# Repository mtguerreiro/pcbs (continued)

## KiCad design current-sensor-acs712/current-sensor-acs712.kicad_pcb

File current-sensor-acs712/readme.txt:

Current sensor
--------------

The board was designed with ACS712 in mind. However, it will work with the following ACS sensors:
- ACS711
- ACS712
- ACS725
- ACS730
- ACS70331
- ACS71240

The only difference is pin 6, which can be a filter, NC, or a fault signal. Beforing using one of these sensors, consult the datasheet for the proper configuration on the board.

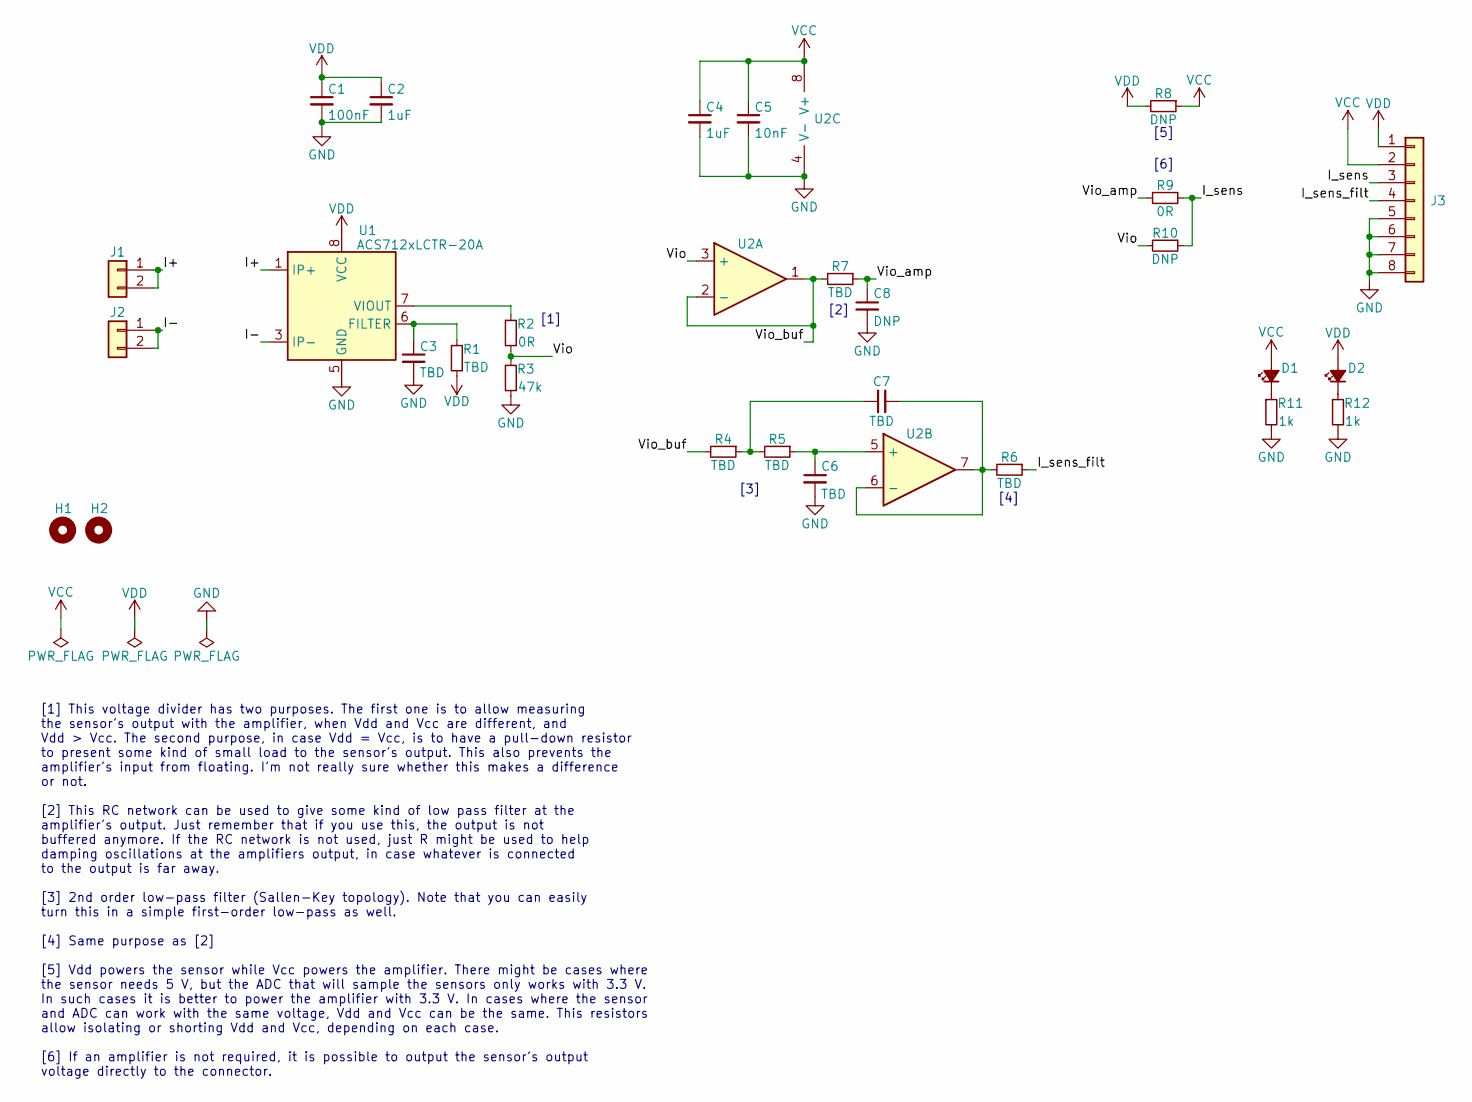
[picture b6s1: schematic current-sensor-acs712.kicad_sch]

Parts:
C1: 100nF; C_0805_2012Metric_Pad1.18x1.45mm_HandSolder
C2, C4: 1uF; C_0805_2012Metric_Pad1.18x1.45mm_HandSolder
C3, C6, C7: TBD; C_0805_2012Metric_Pad1.18x1.45mm_HandSolder
C5: 10nF; C_0805_2012Metric_Pad1.18x1.45mm_HandSolder
C8: DNP; C_0805_2012Metric_Pad1.18x1.45mm_HandSolder
D1, D2: LED_Small_Filled; LED_0805_2012Metric_Pad1.15x1.40mm_HandSolder
H1, H2: MountingHole; MountingHole_3.2mm_M3
J1, J2: Conn_01x02; TerminalBlock_Phoenix_MKDS-1,5-2-5.08_1x02_P5.08mm_Horizont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
J3: Conn_01x08; PinHeader_1x08_P2.54mm_Vertical
R1, R4, R5, R6, R7: TBD; R_0805_2012Metric_Pad1.20x1.40mm_HandSolder
R2, R9: 0R; R_0805_2012Metric_Pad1.20x1.40mm_HandSolder
R3: 47k; R_0805_2012Metric_Pad1.20x1.40mm_HandSolder
R8, R10: DNP; R_0805_2012Metric_Pad1.20x1.40mm_HandSolder
R11, R12: 1k; R_0805_2012Metric_Pad1.20x1.40mm_HandSolder
U1: ACS712xLCTR-20A; SOIC-8_3.9x4.9mm_P1.27mm
U2: Opamp_Dual; SOIC-8_3.9x4.9mm_P1.27mm

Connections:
/I+: J1.1, J1.2, U1.1 (IP+), U1.2 (IP+)
/I-: J2.1, J2.2, U1.3 (IP-), U1.4 (IP-)
/I_sens: J3.3, R9.1, R10.1
/I_sens_filt: J3.4, R6.1
/Vio: R2.2, R3.1, R10.2, U2.3 (+)
/Vio_amp: C8.1, R7.1, R9.2
/Vio_buf: R4.2, R7.2, U2.1, U2.2 (-)
GND: C1.2, C2.2, C3.2, C4.2, C5.2, C6.2, C8.2, J3.5, J3.6, J3.7, J3.8, R3.2, R11.2, R12.2, U1.5 (GND), U2.4 (V-)
unnamed: C3.1, R1.1, U1.6 (FILTER)
unnamed: C6.1, R5.1, U2.5 (+)
unnamed: C7.1, R4.1, R5.2
unnamed: C7.2, R6.2, U2.6 (-), U2.7
unnamed: D1.1 (K), R11.1
unnamed: D2.1 (K), R12.1
unnamed: R2.1, U1.7 (VIOUT)
VCC: C4.1, C5.1, D1.2 (A), J3.2, R8.1, U2.8 (V+)
VDD: C1.1, C2.1, D2.2 (A), J3.1, R1.2, R8.2, U1.8 (VCC)

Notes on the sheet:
[4]
[1]
[3]
[2]
[1] This voltage divider has two purposes. The first one is to allow measuring the sensor's output with the amplifier, when Vdd and Vcc are different, and Vdd > Vcc. The second purpose, in case Vdd = Vcc, is to have a pull-down resistor to present some kind of small load to the sensor's output. Thi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
[6]
[5]

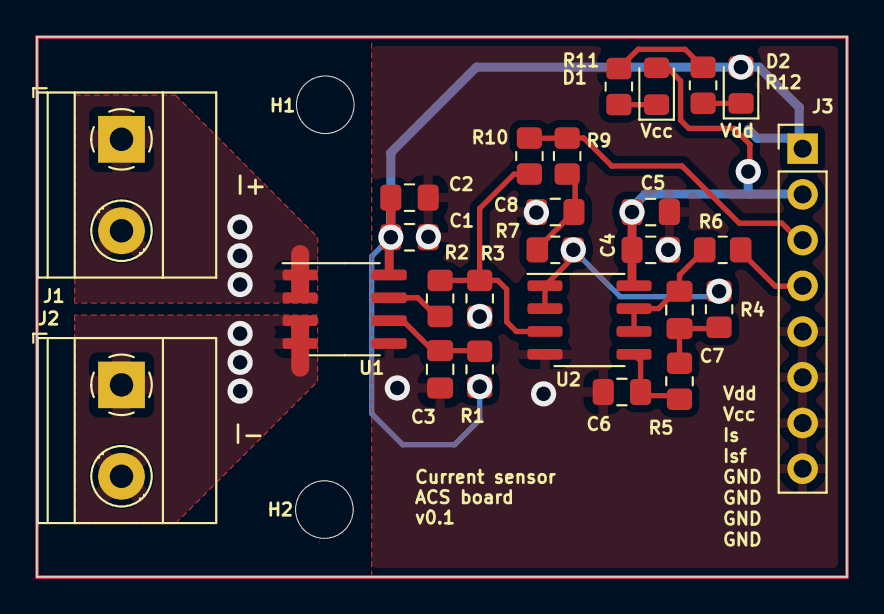
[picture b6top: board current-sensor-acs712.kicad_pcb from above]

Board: 2 copper layers, 45.0 x 30.0 mm, 29 parts (1 on the bottom side), 17 nets.

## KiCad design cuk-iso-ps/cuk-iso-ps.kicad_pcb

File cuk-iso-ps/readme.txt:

Current sensor
--------------

The board was designed with ACS730-20AB in mind. However, it will work with the following ACS sensors:
- ACS711
- ACS712
- ACS725
- ACS730
- ACS70331
- ACS71240

The only difference is pin 6, which can be a filter, NC, or a fault signal. Beforing using one of these sensors, consult the datasheet for the proper configuration on the board.

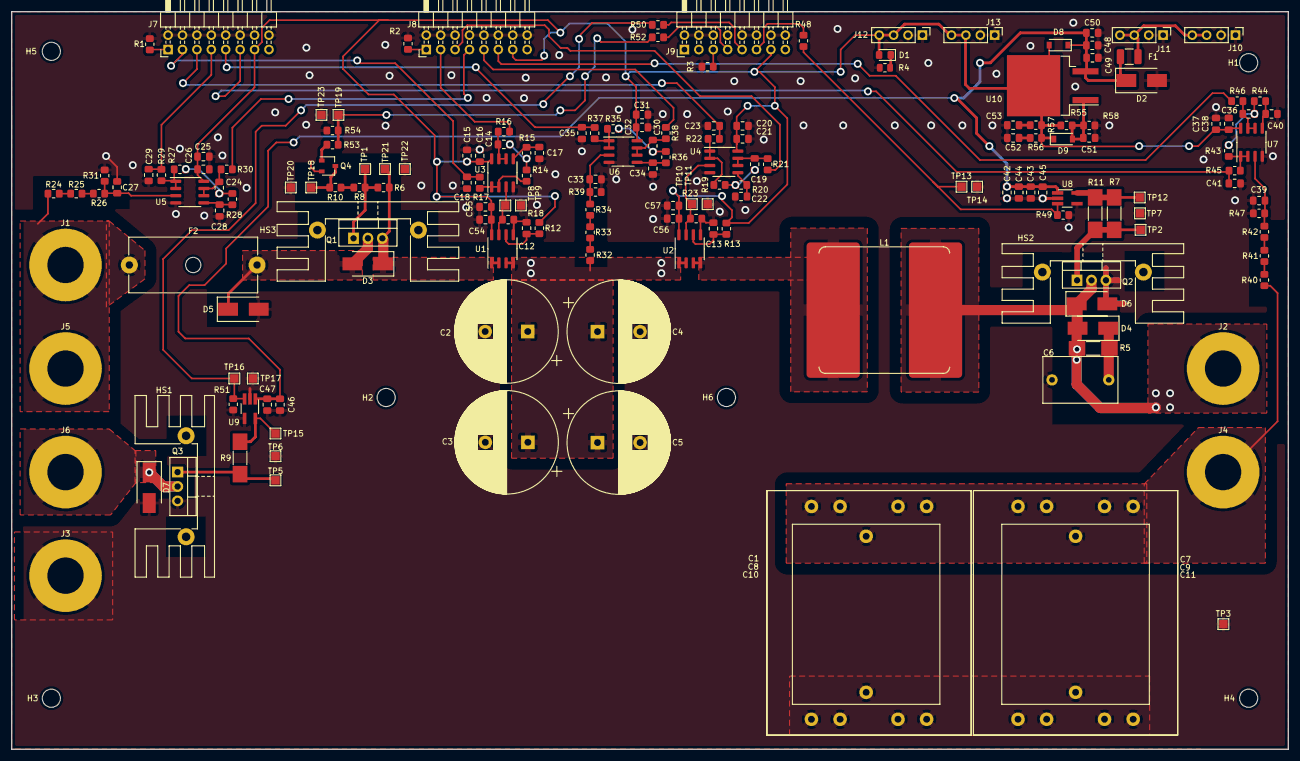
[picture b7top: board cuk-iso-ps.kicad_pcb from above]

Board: 2 copper layers, 225.0 x 130.0 mm, 185 parts (0 on the bottom side), 77 nets.

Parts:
C1, C7: 13uF; C_Rect_L31.5mm_W26.0mm_P27.50mm_Film
C2, C3, C4, C5: TBD; CP_Radial_D18.0mm_P7.50mm
C6: 10nF; C_Rect_L13.0mm_W8.0mm_P10.00mm_FKS3_FKP3_MKS4
C8, C9: 13uF; C_Rect_L42.0mm_W38.0mm_P37.50mm_S10.2mm_Film
C10, C11: 13uF; C_Rect_L42.0mm_W38.0mm_P37.50mm_S20.3mm_Film
C12, C13, C14, C17, C19, C22, C24, C28, C30, C34, C36, C40: TBD; C_0805_2012Metric_Pad1.18x1.45mm_HandSolder
C15, C20, C25, C31, C37, C55, C57: 1uF; C_0805_2012Metric_Pad1.18x1.45mm_HandSolder
C16, C21, C26, C32, C38: 10nF; C_0805_2012Metric_Pad1.18x1.45mm_HandSolder
C18, C23, C27, C29, C33, C35, C39, C41: DNP; C_0805_2012Metric_Pad1.18x1.45mm_HandSolder
C42, C43, C44, C46, C48, C49, C52, C53: 10uF; C_0805_2012Metric_Pad1.18x1.45mm_HandSolder
C45, C47, C50, C51, C54, C56: 100nF; C_0805_2012Metric_Pad1.18x1.45mm_HandSolder
D1: LED_Small_Filled; LED_0805_2012Metric_Pad1.15x1.40mm_HandSolder
D2, D5: D_Zener_Small_Filled; D_SMB_Handsoldering
D3, D4, D6, D7: D_Schottky_Small_Filled; D_SMB_Handsoldering
D8, D9: 1N4148; D_SOD-123
F1: Polyfuse; R_1210_3225Metric_Pad1.30x2.65mm_HandSolder
F2: Fuse_Small; Fuseholder_Cylinder-5x20mm_Schurter_0031_8201_Horizontal_Op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
H1, H2, H3, H4, H5, H6: MountingHole; MountingHole_3.2mm_M3
HS1, HS2, HS3: Heatsink_Pad_2Pin; Heatsink_Stonecold_HS-132_32x14mm_2xFixation1.5mm_2pins
J1, J2, J3, J4, J5, J6: MountingHole_6.4mm_M6_Pad
J7, J8, J9: Conn_02x08_Odd_Even; PinHeader_2x08_P2.54mm_Horizontal
J10, J11, J12, J13: Conn_01x04; PinHeader_1x04_P2.54mm_Vertical
L1: L; L_Bourns_SRP2313AA_24x24
Q1: Q_PMOS_GDS; TO-220-3_Vertical
Q2, Q3: Q_NMOS_GDS; TO-220-3_Vertical
Q4: SOT-23W
R1, R2: 0R; R_0805_2012Metric_Pad1.20x1.40mm_HandSolder
R3: DNP; R_0805_2012Metric_Pad1.20x1.40mm_HandSolder
R4: 2k; R_0805_2012Metric
R5: 20R; R_MELF_MMB-0207_HandSoldering
R6, R8, R10, R12, R13, R14, R15, R16, R17, R19, R20, R21, R22, R24, R25, R26, R27, R28, R29, R30, R31, R32, R33, R34, R35, R36, R37, R38, R39, R40, R41, R42, R43, R44, R45, R46, R47, R48, R50, R52, R55, R56, R57, R58: TBD; R_0805_2012Metric_Pad1.20x1.40mm_HandSolder
R7, R9, R11: 3R3; R_MELF_MMB-0207_HandSoldering
R18, R23: 47k; R_0805_2012Metric_Pad1.20x1.40mm_HandSolder
R49, R51, R54: 100k; R_0805_2012Metric_Pad1.20x1.40mm_HandSolder
R53: 4k7; R_0805_2012Metric_Pad1.20x1.40mm_HandSolder
TP1, TP2, TP3, TP5, TP6, TP7, TP8, TP9, TP10, TP11, TP12, TP13, TP14, TP15, TP16, TP17, TP18, TP19, TP20, TP21, TP22, TP23: TestPoint_Small; TestPoint_Pad_1.5x1.5mm
U1, U2: ACS730xLCTR-20AB; SOIC-8_3.9x4.9mm_P1.27mm
U3, U4, U5, U6, U7: Opamp_Dual; SOIC-8_3.9x4.9mm_P1.27mm
U8, U9: DGD0211C; TSOT-23-5_HandSoldering
U10: LM317; TO-263-2

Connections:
/Current measurements/IL current sensor conditioning/in_buf: R19.2, R22.2, U4.1, U4.2 (-)
/Current measurements/IL_sens: R23.1, TP10.1, U2.7 (VIOUT), U4.3 (+)
/Current measurements/Iio current sensor conditioning/in_buf: R14.2, R17.2, U3.1, U3.2 (-)
/Current measurements/Iio_sens: R18.1, TP8.1, U1.7 (VIOUT), U3.3 (+)
/IL+: C2.1, C3.1, C4.1, C5.1, R32.2, U1.3 (IP-), U1.4 (IP-), U2.1 (IP+), U2.2 (IP+)
/IL-: L1.1, U2.3 (IP-), U2.4 (IP-)
/IL_meas: C23.1, J7.5, R22.1
/IL_meas_filt: J8.5, R21.1
/Iio+: D3.1 (K), Q1.3 (S), R6.2, TP21.1, U1.1 (IP+), U1.2 (IP+)
/Iio_meas: C18.1, J7.3, R17.1
/Iio_meas_filt: J8.3, R16.1
/Power stage/L-: D7.1 (K), J6.1, Q3.2 (D)
/Power stage/TF+: D4.2 (A), D6.1 (K), J2.1, L1.2, Q2.2 (D), R5.1
/SW_C: R7.1, R11.1, TP12.1, U8.5 (OUT)
/SW_C_D: J9.11, R48.2
/SW_L: R9.2, TP15.1, U9.5 (OUT)
/SW_L_D: J9.9, R50.2
/SW_O: Q4.3 (C), R10.1, TP18.1
/SW_O_D: J9.7, R52.2
/Vc: C1.2, C7.2, C8.2, C9.2, C10.2, C11.2, J4.1, R40.2
/Vc_meas: C41.1, J7.11, R45.1
/Vc_meas_filt: J8.11, R46.1
/Vdc_meas: C35.1, J7.9, R37.1
/Vdc_meas_filt: J8.9, R38.1
/Vdd_in: F1.1, J10.3, J10.4, J11.3, J11.4
/Vio: F2.1, J1.1, J5.1, R24.2
/Vio_meas: C29.1, J7.7, R29.1
/Vio_meas_filt: J8.7, R30.1
/Voltage measurements/Vc voltage conditioning/in_buf: R43.2, R45.2, U7.1, U7.2 (-)
/Voltage measurements/Vdc voltage conditioning/in_buf: R35.2, R37.2, U6.1, U6.2 (-)
/Voltage measurements/Vio voltage conditioning/in_buf: R27.2, R29.2, U5.1, U5.2 (-)
GND: C1.1, C2.2, C3.2, C4.2, C5.2, C6.1, C7.1, C8.1, C9.1, C10.1, C11.1, C12.2, C13.2, C15.2, C16.2, C17.2, C18.2, C20.2, C21.2, C22.2, C23.2, C25.2, C26.2, C27.2, C28.2, C29.2, C31.2, C32.2, C33.2, C34.2, C35.2, C37.2, C38.2, C39.2, C40.2, C41.2, C42.2, C43.2, C44.2, C45.2, C46.2, C47.2, C48.2, C49.2, C50.2, C51.2, C52.2, C53.2, C54.2, C55.2, C56.2, C57.2, D2.2 (A), D5.2 (A), D6.2 (A), D7.2 (A), J3.1, J7.2, J7.4, J7.6, J7.8, J7.10, J7.12, J7.14, J7.16, J8.2, J8.4, J8.6, J8.8, J8.10, J8.12, J8.14, J8.16, J9.2, J9.4, J9.6, J9.8, J9.10, J9.12, J9.14, J9.16, J10.1, J10.2, J11.1, J11.2, J12.1, J12.2, J13.1, J13.2, Q2.3 (S), Q3.3 (S), Q4.2 (E), R1.1, R2.1, R3.1, R4.2, R18.2, R23.2, R31.2, R39.2, R47.2, R49.2, R51.2, R54.2, R58.2, TP3.1, TP6.1, TP7.1, TP9.1, TP11.1, TP14.1, TP17.1, TP20.1, TP22.1, TP23.1, U1.5 (GND), U2.5 (GND), U3.4 (V-), U4.4 (V-), U5.4 (V-), U6.4 (V-), U7.4 (V-), U8.2 (GND), U8.4 (IN*), U9.2 (GND), U9.4 (IN*)
unnamed: C6.2, D4.1 (K), R5.2
unnamed: C12.1, R12.1, U1.6 (VZCR)
unnamed: C13.1, R13.1, U2.6 (VZCR)
unnamed: C14.1, R14.1, R15.2
unnamed: C14.2, R16.2, U3.6 (-), U3.7
unnamed: C17.1, R15.1, U3.5 (+)
unnamed: C19.1, R19.1, R20.2
unnamed: C19.2, R21.2, U4.6 (-), U4.7
unnamed: C22.1, R20.1, U4.5 (+)
unnamed: C24.1, R27.1, R28.2
unnamed: C24.2, R30.2, U5.6 (-), U5.7
unnamed: C27.1, R26.1, R31.1, U5.3 (+)
unnamed: C28.1, R28.1, U5.5 (+)
unnamed: C30.1, R35.1, R36.2
unnamed: C30.2, R38.2, U6.6 (-), U6.7
unnamed: C33.1, R34.1, R39.1, U6.3 (+)
unnamed: C34.1, R36.1, U6.5 (+)
unnamed: C36.1, R43.1, R44.2
unnamed: C36.2, R46.2, U7.6 (-), U7.7
unnamed: C39.1, R42.1, R47.1, U7.3 (+)
unnamed: C40.1, R44.1, U7.5 (+)
unnamed: C51.1, D9.2 (A), R55.2, R58.1, U10.1 (ADJ)
unnamed: C52.1, R56.2
unnamed: C53.1, R57.2
unnamed: D1.1 (K), R4.1
unnamed: D3.2 (A), D5.1 (K), F2.2, Q1.2 (D)
unnamed: J8.1, R2.2
unnamed: J9.5, R3.2
unnamed: Q1.1 (G), R6.1, R8.1, TP1.1
unnamed: Q2.1 (G), R7.2, R11.2, TP2.1
unnamed: Q3.1 (G), R9.1, TP5.1
unnamed: Q4.1 (B), R53.1
unnamed: J7.1, R1.2
unnamed: R8.2, R10.2
unnamed: R24.1, R25.2
unnamed: R25.1, R26.2
unnamed: R32.1, R33.2
unnamed: R33.1, R34.2
unnamed: R40.1, R41.2
unnamed: R41.1, R42.2
unnamed: R48.1, R49.1, TP13.1, U8.3 (IN)
unnamed: R50.1, R51.1, TP16.1, U9.3 (IN)
unnamed: R52.1, R53.2, R54.1, TP19.1
VCC: C15.1, C16.1, C20.1, C21.1, C25.1, C26.1, C31.1, C32.1, C37.1, C38.1, C54.1, C55.1, C56.1, C57.1, D1.2 (A), D8.2 (A), D9.1 (K), J7.13, J8.13, J9.13, J12.3, J12.4, J13.3, J13.4, R12.2, R13.2, R55.1, R56.1, R57.1, U1.8 (VCC), U2.8 (VCC), U3.8 (V+), U4.8 (V+), U5.8 (V+), U6.8 (V+), U7.8 (V+), U10.2 (VO)
VDD: C42.1, C43.1, C44.1, C45.1, C46.1, C47.1, C48.1, C49.1, C50.1, D2.1 (K), D8.1 (K), F1.2, U8.1 (Vcc), U9.1 (Vcc), U10.3 (VI)

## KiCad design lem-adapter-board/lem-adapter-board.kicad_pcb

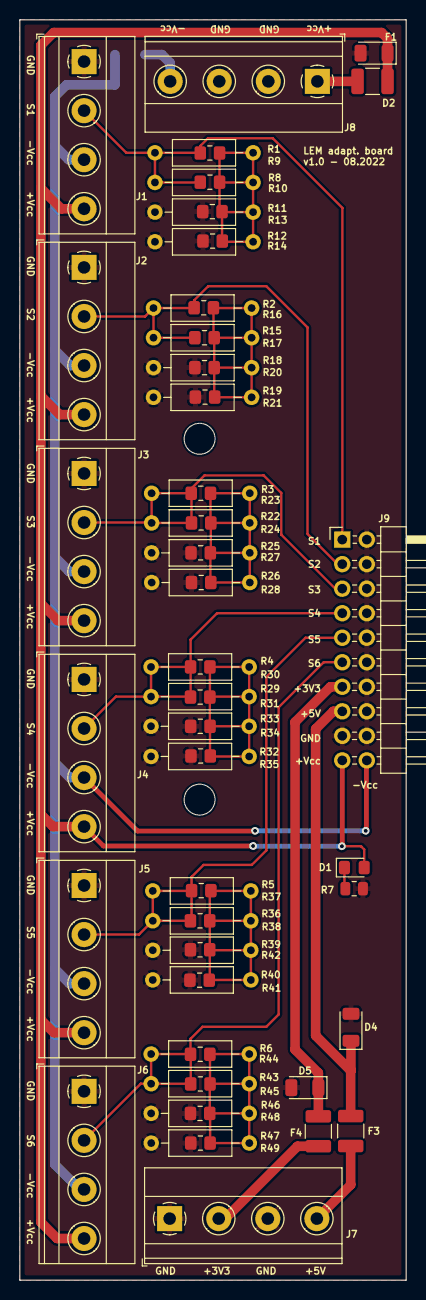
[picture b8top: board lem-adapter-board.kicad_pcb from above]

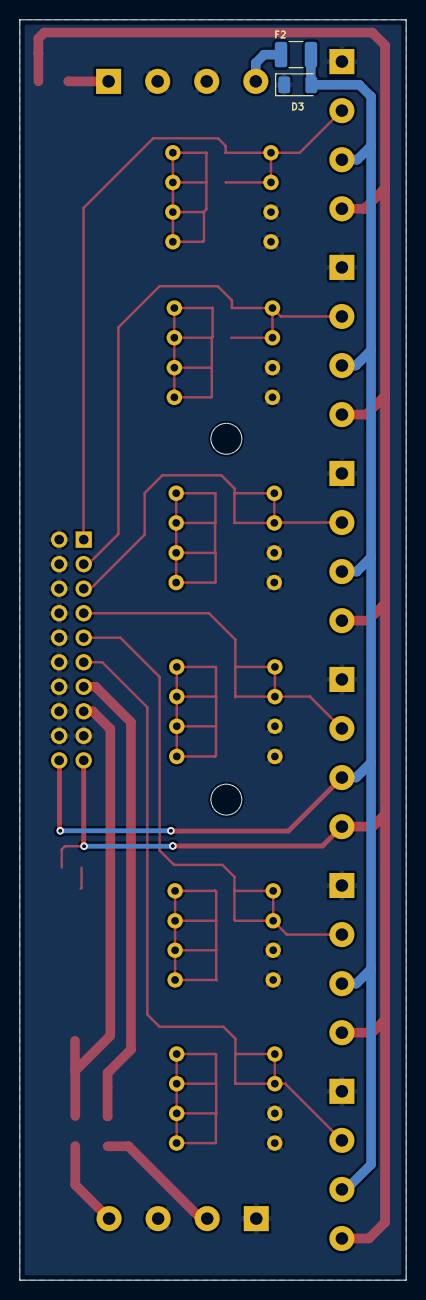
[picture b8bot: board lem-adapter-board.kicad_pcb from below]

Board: 2 copper layers, 40.0 x 130.5 mm, 67 parts (2 on the bottom side), 22 nets.

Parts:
D1: LED; LED_0805_2012Metric_Pad1.15x1.40mm_HandSolder
D2, D3, D4, D5: D_Zener; D_1206_3216Metric
F1, F2, F3, F4: Polyfuse; R_1210_3225Metric_Pad1.30x2.65mm_HandSolder
J1, J2, J3, J4, J5, J6, J7, J8: Conn_01x04; TerminalBlock_Phoenix_MKDS-1,5-4-5.08_1x04_P5.08mm_Horizont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
J9: Conn_02x10_Odd_Even; PinHeader_2x10_P2.54mm_Horizontal
R1, R2, R3, R4, R5, R6, R8, R11, R12, R15, R18, R19, R22, R25, R26, R29, R32, R33, R36, R39, R40, R43, R46, R47: DNP; R_0805_2012Metric_Pad1.20x1.40mm_HandSolder
R7: TBD; R_0805_2012Metric
R9, R10, R13, R14, R16, R17, R20, R21, R23, R24, R27, R28, R30, R31, R34, R35, R37, R38, R41, R42, R44, R45, R48, R49: DNP; R_Axial_DIN0207_L6.3mm_D2.5mm_P10.16mm_Horizontal

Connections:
+3V3: D5.1 (K), F4.2, J9.13
+3V3A: F4.1, J7.2
+5V: D4.1 (K), F3.2, J9.15
+5VA: F3.1, J7.4
+VCC: D1.2 (A), D2.1 (K), F1.2, J1.4, J2.4, J3.4, J4.4, J5.4, J6.4, J9.19
+VDD: F1.1, J8.1
-VCC: D3.2 (A), F2.2, J1.3, J2.3, J3.3, J4.3, J5.3, J6.3, J9.20
-VDD: F2.1, J8.4
/S1: J1.2, J9.1, R1.2, R8.2, R9.2, R10.2
/S2: J2.2, J9.3, R2.2, R15.2, R16.2, R17.2
/S3: J3.2, J9.5, R3.2, R22.2, R23.2, R24.2
/S4: J4.2, J9.7, R4.2, R29.2, R30.2, R31.2
/S5: J5.2, J9.9, R5.2, R36.2, R37.2, R38.2
/S6: J6.2, J9.11, R6.2, R43.2, R44.2, R45.2
GND: D2.2 (A), D3.1 (K), D4.2 (A), D5.2 (A), J1.1, J2.1, J3.1, J4.1, J5.1, J6.1, J7.1, J7.3, J8.2, J8.3, J9.2, J9.4, J9.6, J9.8, J9.10, J9.12, J9.14, J9.16, J9.17, J9.18, R7.2, R11.1, R12.1, R13.1, R14.1, R18.1, R19.1, R20.1, R21.1, R25.1, R26.1, R27.1, R28.1, R32.1, R33.1, R34.1, R35.1, R39.1, R40.1, R41.1, R42.1, R46.1, R47.1, R48.1, R49.1
unnamed: D1.1 (K), R7.1
unnamed: R1.1, R8.1, R9.1, R10.1, R11.2, R12.2, R13.2, R14.2
unnamed: R2.1, R15.1, R16.1, R17.1, R18.2, R19.2, R20.2, R21.2
unnamed: R3.1, R22.1, R23.1, R24.1, R25.2, R26.2, R27.2, R28.2
unnamed: R4.1, R29.1, R30.1, R31.1, R32.2, R33.2, R34.2, R35.2
unnamed: R5.1, R36.1, R37.1, R38.1, R39.2, R40.2, R41.2, R42.2
unnamed: R6.1, R43.1, R44.1, R45.1, R46.2, R47.2, R48.2, R49.2

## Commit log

2022-07-13 Added relay precharge module
2022-07-13 Added gate driver lib
2022-07-14 Added HFBR receiver symbol
2022-07-15 Added 3D model and sim to relay precharge module
2022-07-15 Finishing switched load module
2022-07-15 Added MIC4102
2022-07-20 Added switched load board
2022-07-20 Finalizing relay-pc-module
2022-07-20 Added sim for load switch
2022-07-20 Added diode for switched load module
2022-07-21 Added LEDs to relay pc module
2022-07-21 Added LEDs to switched load module
2022-07-24 Added generic dip24 dcdc
2022-07-24 AFE meas. supply
2022-07-24 Started working on gate driver
2022-07-25 Added/fixed mounting holes
2022-07-26 Added design rules to afe power supply
2022-08-01 Added six-channel amplifier board
2022-08-01 Added symbol for a generic single-channel SPI ADC
2022-08-03 Added 6-channel adc board
2022-08-03 Displaced track in adc 6-channel board
2022-08-03 Added optic transmitter
2022-08-04 Corrected pin type in optic tx lib
2022-08-04 Added footprint to optic tx symbol
2022-08-05 Added 3D symbol for fiber connectors
2022-08-05 Working on adc-fiber interface
2022-08-07 Initial version of adc-fiber board
2022-08-07 Updated boards with dates, silk, mounting holes
2022-08-09 Added + and - vcc as custom power symbols
2022-08-09 Added buffer board
2022-08-09 Removed db9 connector from relay-pc module
2022-08-13 Added power and generic digital buffer symbols
2022-08-13 Added AFE shield
2022-08-15 Simulating hb-gate-driver
2022-08-19 Fixed afe shield connector
2022-08-19 Connected 3V3A and 3V3 in afe shield
2022-08-20 Improved gate driver sim
2022-08-20 Started working on optic transceiver
2022-08-22 Finalized optic boards, modified sil in adc-fiber interface board
2022-08-26 Added custom vdd power symbols
2022-08-26 Added lem adapter board
2022-08-27 Inverter relay module connector
2022-08-27 Generated gerber files relay module
2022-08-27 Adjusted clearence for low-side switch module
2022-08-27 Generated gerber files for low-side switch module
2022-08-27 Added fuse and generated gerber files for afe power supply
2022-08-29 Updated silkscreen and gerber files on relay pc module
2022-08-29 Corrected relay connector and generated gerber files for afe shield
2022-08-29 Changed order in lem adapter connector
2022-08-29 Generated gerber files for lem adapter board
2022-08-29 Generated gerber files for analog-buffer board
2022-08-29 Saving plot options for analog-buffer
2022-08-29 Regenerated gerberf iles for analog-buffer board
2022-08-29 Generated gerber files for amplifier board
2022-08-29 Generated gerber for adc-board
2022-08-29 Generated gerber files for adc-fiber-interface board
2022-08-29 Generated gerber files for optic-transceiver board
2022-10-16 Schematics for MIC4102 gate driver
2022-12-13 Created custom bom scripts
2022-12-13 Created bom for adc board
2022-12-13 Created BOM for adc fiber interface board
2022-12-13 Created BOM for afe shield
2022-12-13 Created bom for afe power supply
2022-12-13 Updated gain values and created bom for amplifier board
2022-12-13 Created bom for analog buffer board
2022-12-13 Created bom for lem adapter board
2022-12-13 Bom for optic transceiver board
2022-12-13 Creted bom for relay module
2022-12-13 Bom for low-side switch board
2022-12-15 Added ideas and issues
2023-07-11 Added custom footprints for caps, res and inductors
2023-08-08 Added VDD1, GND1, VDD2, GND2 power symbols
2023-08-08 Initial version of cuk power stage
2023-08-12 Added VDDB and GNDB power symbols
2023-08-12 Digital isolator 2T6R board for in house fab
2023-08-16 Digital isolator 6T2R board for in house fab
2023-08-23 Added arduino lib from Alarm-Siren github repo
2023-08-23 Added edge copper tracks for cuk for in-house fab
2023-08-23 Added copper tracks to digital iso 2t6r board for in-house fab
2023-08-23 Copper tracks as edge cuts to digital iso 6t2r for in-house fab
2023-08-23 Created Pynq Z2 adapter board
2023-08-29 Added pull up resistor to digital isolator 2t6r board
2023-08-29 Added pull up resistors to dig iso 6t2r board
2023-09-28 Generated gerbers of pynq adapter for in house production
2023-09-28 Gerber files for digital isolator 2t6r for in house fab
2023-09-28 Gerber files for cuk power for in house fab
2023-09-28 Generated gerber for digital isolator 6t2r for in house fab
2023-10-25 Working on mic4102 schematics
2023-10-29 Initial schematics for acs board
2023-11-05 Adjusted snubber text in cuk iso
2023-11-05 Added improvements for digital isolator boards
2023-11-12 Finished schematics for acs board, started pcb
2023-11-19 Finishing acs712 board
2023-11-23 Added power leds suggestion to cuk iso
2023-11-23 Finished acs pcb
2023-11-23 Generated gerbers of acs board for in house fab
2024-02-05 Creating schematic for pico and supply interface
2024-03-07 Working on pico itm interface
2024-03-10 Finishing schematics of pico itm if
2024-03-10 Added docs for subcircuits
2024-03-10 Passing ERC
2024-03-12 Expanded unused pico pins
2024-03-12 Fixed Pico and DAC footprints
2024-03-15 Working on pcb for pi pico it
2024-03-22 Finishing pi pico itm if pcb
2024-03-22 Created gerber files for in house fab
2024-05-02 Added list of issues for it if board
2024-05-02 Adapted dig iso 6t2r for jlcpcb
2024-05-02 Generated new gerbers for dig iso 2t6r
2024-05-02 Adapted pcb and generated gerbers for jlcpcb for dig iso 6t2r
2024-05-02 Saving gerber settings for 6t2r
2024-05-03 Adapted and generated gerber files for pynq rpi adapter for jlcpcb
2024-05-12 Created pynq buck adapter
2024-06-16 Initial buck-boost plat files
2024-07-06 Sim for buck-boost circuit
2024-07-14 Initial doc files
2024-07-21 Diagram of gate driver
2024-07-28 Working on diagrams for adc board docs
2024-07-28 Working on power stage of buck-boost plat
2024-07-28 Initial version of docs for adc board
2024-07-31 Preparing docs for gh pages
2024-07-31 deploy: a134106d05d90f406177a17ca4cb45505ea1c51b
2024-08-04 Added license
2024-08-04 Docs for dig-iso-2t6r board
2024-08-04 deploy: 701739341820c31cc4c2ef15e8e42d169d13b744
2024-08-10 Initial docs for amplifier board
2024-08-11 Schematics for power stage
2024-08-16 Docs for amplifier board
2024-08-16 deploy: 652b88d2230c33255a44c66fd2a55db3c6484ee6
2024-08-17 Created generic film cap footprint
2024-08-31 Updating schematics notes
2024-08-31 Documentation for dig iso 6t2r board
2024-08-31 deploy: 95e9d44d22bc2ecbe4a0146ee97ded165afaf1f2
2024-09-01 Working on gate drivers of buck boost platform
2024-09-07 Initial docs for pynq rpi board
2024-09-07 Changed img to media folder, updated examples
2024-09-07 deploy: 610ee66daa138d720240bc771393ad9c3c1e6c30
2024-09-08 Added load switch and relay drivers
2024-09-22 Initial docs for cuk-iso
2024-09-29 Working on docs for cuk, fixed scaling issue of pinouts
2024-09-29 Adding connectors, test points to gate drivers
2024-10-05 Finishing docs for cuk iso
2024-10-05 deploy: 529f053ed378943082b51160122a61c4b2accdf4
2024-10-06 Changing docs to master
2024-10-18 Adding current and voltage measurements blocks
2024-10-25 Editing sheets(Power labels, sheet color, adding text), Adding information in the sensor sheets
2024-10-31 Coil footprint added. New IC for CL_Regulator_Switching
2024-10-31 Adding supply block
2024-11-07 The changes indicated in the text document Review. 05.11.2024 were implemented. Missing footprints were added
2024-11-29 Some errors in the schematics were corrected. PCB file V1.0
2024-12-06 The recommendations discussed in the meeting must be implemented. The placement of some components must be improved.
2024-12-08 V1.0 trying to improve the placement of the input relay
2024-12-11 Changing the position of the Gate drivers
2024-12-15 V1.0 finished. Teardrops were added.
2024-12-16 Updated V1.0. Some changes regarding review. 16.12.2024 still to be done
2024-12-17 I forgot to attach the fiel Overview ....
2024-12-18 V1.1. Changes regarding to Review 16.12.2024
2024-12-19 V1.2. New relay foot print added with 3D figure
2024-12-19 v1.2. Small modifications in the silkscreen layer
2024-12-19 V1.2. Fabrication files were generated
2025-01-17 Adding dead time to ltspice simulation of buck and boost
2025-02-28 Updating Cuk ltspice simulation
2025-05-04 Updating cuk docs
2025-05-11 Updating cuk photo
2025-05-11 deploy: 569c220439bc684ed0846e35afa2f7f939a29ba7
